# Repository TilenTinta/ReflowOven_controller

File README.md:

# Reflow Oven Controller

An open-source controller for converting a kitchen toaster oven into a reflow oven.

## Overview

This project consists of a PCB and firmware to convert a classic toaster oven into a temperature-controlled oven for PCB reflow.

### Oven Modes
- **Reflow** - Follows a predefined temperature curve for optimal PCB reflow.
- **Dry** - Maintains a defined temperature for a set duration (useful for drying components, filaments, etc.).

The oven used in this build is a budget-friendly (**40€**) **9L toaster oven** with two quartz heating elements (**BROCK TO9001B**). Despite initial concerns about heating speed, the small chamber allows it to reach the required temperatures quickly. The oven has been additionally insulated for improved performance.

A **solid-state relay (SSR)** is used for controlling the heating elements, and a **12V 5A power supply** powers the entire electronics system.

---

## PCB

The PCB is a **two-layer board** with components on only one side (**except for the LCD connector, which is on the opposite side**). The board has the **same dimensions and mounting hole positions as the LCD**, allowing them to be stacked using a **3D-printed spacer**.

The LCD used in this build is a **3.5-inch TFT LCD Display Module (320x480) with SPI Interface and Touch Screen (ILI9488 v2).**

### PCB Features
- **Safety switch** for 12V
- **Voltage measurement** (input and buck output)
- **Overtemperature protection** via NTC sensor
- **Input protection** (fuse and reverse polarity protection)
- **Max input voltage: 23V**
- **AUX1 and AUX2** (can handle up to 45V and 500mA, but limited by PCB input voltage)
- **Supports up to two solid-state relays (SSRs)** (PWM amplitude matches input voltage)
- **Supports up to two K-type thermocouples (MAX31855)**
- **Raw USART output & USB output (CH340G)** for monitoring and calibration
- **USB OTG support** (requires core clock adjustment, affecting timer parameters)
- **External 2MB flash (W25Q16JVSNIQ)** for GUI and fonts
- **SWD port** for programming
- **Buzzer**
- **MCU: STM32F411CEU6**

---

## 3D Models

All parts are printed from **PC plastic** using an **FDM 3D printer**. Alternative plastics can be used, but they must withstand high temperatures. There are two different options for electronics assembly mounting:
- Inside the oven as is in my case. For that you only need to print **Front_frame**

- On the side of the oven. For that you need to print three parts with **external** at the end of model names. Base that screws to the frame has teeth that allows preset angles. For rigit mount use only screw and nut, but you can add a spring under screw head. That will allow setting the angle later.

---

## External Loader

The **External Loader** is a necessary part of the program. It allows **CubeIDE** to upload data (GUI and fonts) to the external flash chip. If you use a different flash chip, modifications are required to meet the new chip's recommendations. The loader program must be included in the main firmware/IDE.

---

## Firmware

The firmware is not fully compatible with the latest version of the PCB. This update addresses mistakes found in the initial version of the board.

### Missing Features
- **Read input voltage**
- **Read buck voltage**
- **Read NTC sensor**
- **Safety switch** (implemented in code but not tested)

For the GUI, **TouchGFX** with standard elements is used. The only custom file is the **background**.

### External Libraries Used
The libraries for **LCD (with touch)** and **external flash (External Loader)** are not originally written by me but include minor modifications to fit this build. The original work was done by **maudeve-it**:

#### LCD Library:
- [YouTube Video](https://www.youtube.com/watch?v=g1siKaPox88)
- [GitHub Repository](https://github.com/maudeve-it/ILI9XXX-XPT2046-STM32)

#### Flash Library:
- [YouTube Video 1](https://www.youtube.com/watch?v=PO_2ZE1NQF0&list=PL6Fwy7aR3zSlZO3OBppHSzDacE4CGgRqO&index=6)
- [YouTube Video 2](https://www.youtube.com/watch?v=KlG2doCkREM)
- [GitHub Repository](https://github.com/maudeve-it/W25Qxxx_SPI_FLASH_STM32)

---

## License
This project is open-source and available under the **MIT License**.

---

## Contributing
Contributions are welcome! Feel free to submit issues or pull requests to improve the project.

---

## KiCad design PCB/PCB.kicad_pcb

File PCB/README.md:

# PCB
PCB is two layer board with components on only one side (connector for the LCD is the only part on other side). 
It is the same size and the holes are in the same position as LCD. With 3D printed spacer can be connected together.
LCD used in these build is 3.5 inch TFT LCD Display Module (320x480) with SPI Interface and Touch Screen - ILI9488 v2<br />
PCB features are:<br />
- Safety switch for 12V
- Voltage measuring: input and buck output
- PCB temperature: NTC for overtemperature protection
- input protection: fuse and reverse polarity protected
- max. input voltage: 23V
- AUX1 and AUX2 can handle up to 45V (can't be achived becouse of PCB input voltage limit), 500mA
- up to two solid state relays - PWM amplitude is the same as input voltage
- up to two K-type thermocouple (MAX31855)
- for calibration and monitoring is available raw USART output and USB output (CH340G)
- supports USB OTG - in case of enabling that function the core clock must be changed and with that all timers parameters
- external 2MB flash (W25Q16JVSNIQ) for all GUI and fonts
- SWD for programming 
- Buzzer
- MCU: STM32F411CEU6

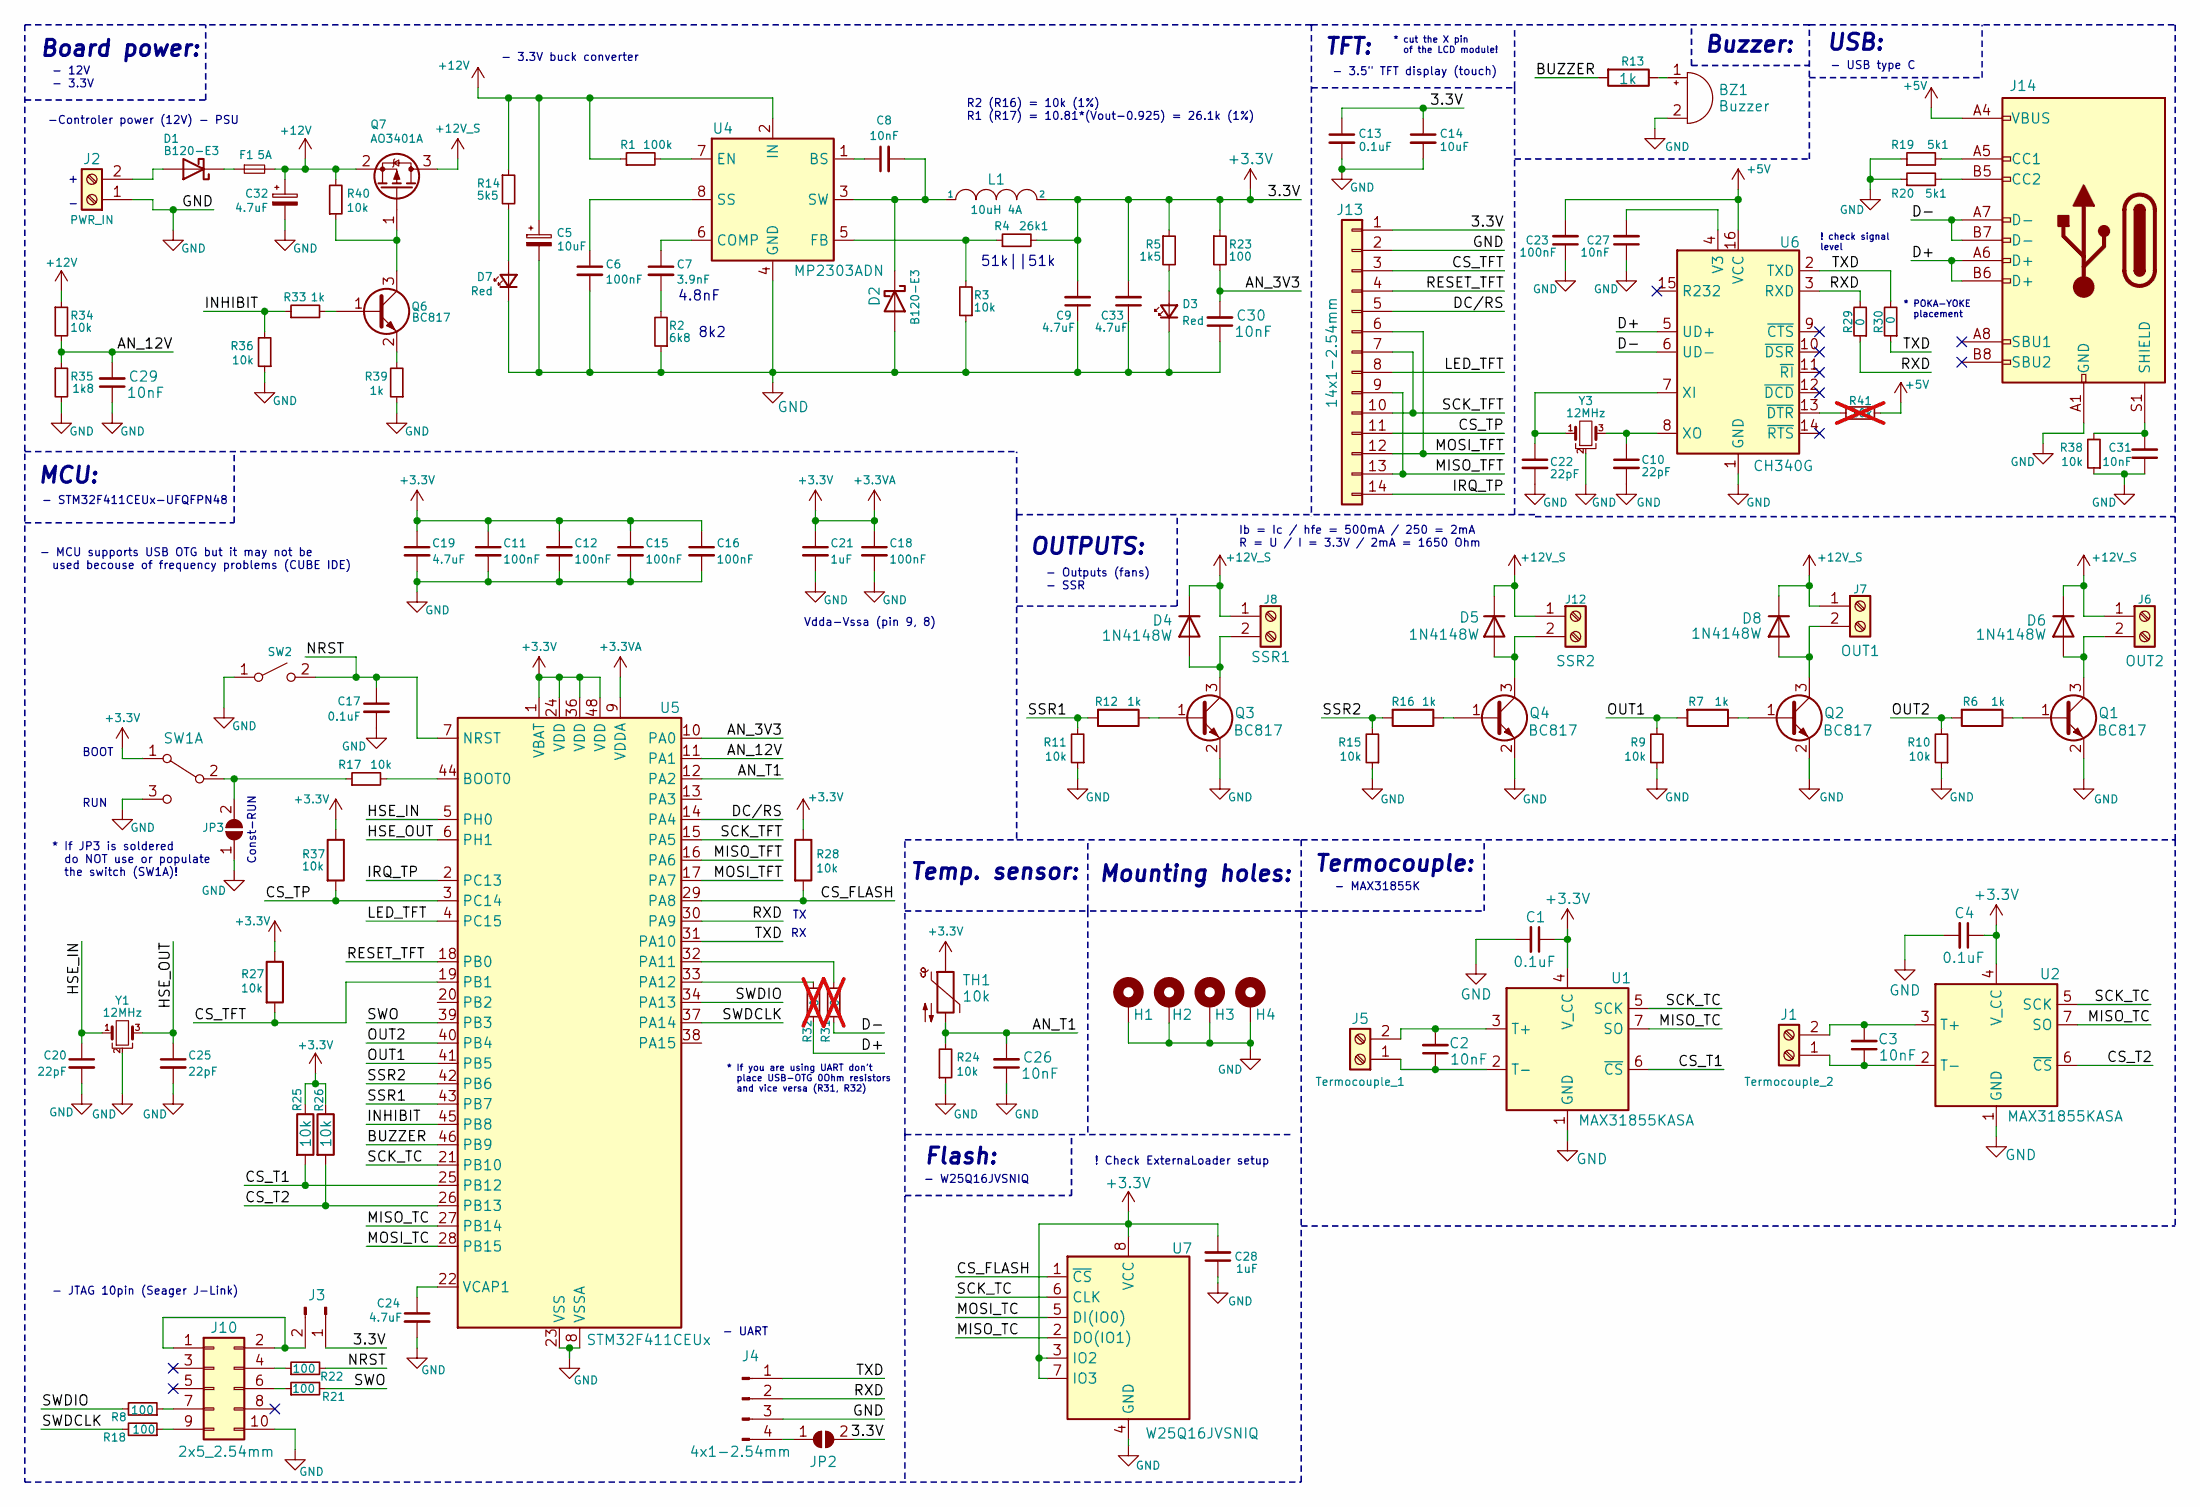
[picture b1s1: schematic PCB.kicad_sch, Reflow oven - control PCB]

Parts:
BZ1: Buzzer; Buzzer_12x9.5RM7.6
C1, C4, C13, C17: 0.1uF; C_0603_1608Metric
C2, C3, C8, C27, C31: 10nF; C_0603_1608Metric
C5: 10uF; CP_EIA-3216-10_Kemet-I
C6, C23: 100nF; C_0603_1608Metric
C7: 3.9nF; C_0603_1608Metric
C9, C33: 4.7uF; C_1206_3216Metric
C10, C20, C22, C25: 22pF; C_0402_1005Metric
C11, C12, C15, C16, C18: 100nF; C_0402_1005Metric
C14: 10uF; C_0603_1608Metric
C19, C24: 4.7uF; C_0402_1005Metric
C21: 1uF; C_0402_1005Metric
C26, C29, C30: 10nF; C_0402_1005Metric
C28: 1uF; C_0603_1608Metric
C32: 4.7uF; CP_Elec_4x5.4
D1, D2: B120-E3; D_SMA
D3, D7: Red; LED_0603_1608Metric
D4, D5, D6, D8: 1N4148W; D_SOD-123
F1: 5A; Fuse_2010_5025Metric_Pad1.52x2.65mm_HandSolder
H1, H2, H3, H4: MountingHole_Pad; MountingHole_3.2mm_M3_DIN965_Pad
J1: Termocouple_2; TerminalBlock_MetzConnect_Type055_RT01502HDWU_1x02_P5.00mm_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
J2: PWR_IN; TerminalBlock_MetzConnect_Type055_RT01502HDWU_1x02_P5.00mm_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
J3: Conn_01x02_Pin; PinHeader_1x02_P2.54mm_Vertical
J4: 4x1-2.54mm; PinHeader_1x04_P2.54mm_Vertical
J5: Termocouple_1; TerminalBlock_MetzConnect_Type055_RT01502HDWU_1x02_P5.00mm_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
J6: OUT2; TerminalBlock_MetzConnect_Type055_RT01502HDWU_1x02_P5.00mm_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
J7: OUT1; TerminalBlock_MetzConnect_Type055_RT01502HDWU_1x02_P5.00mm_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
J8: SSR1; TerminalBlock_MetzConnect_Type055_RT01502HDWU_1x02_P5.00mm_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
J10: 2x5_2.54mm; IDC-Header_2x05_P2.54mm_Vertical
J12: SSR2; TerminalBlock_MetzConnect_Type055_RT01502HDWU_1x02_P5.00mm_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
J13: 14x1-2.54mm; PinSocket_1x14_P2.54mm_Vertical
J14: USB_C_Receptacle_USB2.0; USB_C_Receptacle_XKB_U262-16XN-4BVC11
JP2, JP3: SolderJumper_2_Open; SolderJumper-2_P1.3mm_Open_TrianglePad1.0x1.5mm
L1: 10uH 4A; L_10.4x10.4_H4.8
Q1, Q2, Q3, Q4, Q6: BC817; SOT-23
Q7: AO3401A; SOT-23
R1: 100k; R_0603_1608Metric
R2: 6k8; R_0603_1608Metric
R3, R9, R10, R11, R15, R17, R24, R25, R26, R27, R28, R34, R36, R37, R38, R40: 10k; R_0603_1608Metric
R4: 26k1; R_0603_1608Metric
R5: 1k5; R_0603_1608Metric
R6, R7, R12, R13, R16, R33, R39: 1k; R_0603_1608Metric
R8, R18, R21, R22, R23: 100; R_0603_1608Metric
R14: 5k5; R_0603_1608Metric
R19, R20: 5k1; R_0603_1608Metric
R29, R30: 0; R_0603_1608Metric
R31, R32: 0; R_0603_1608Metric; not fitted
R35: 1k8; R_0603_1608Metric
R41: 10k; R_0603_1608Metric; not fitted
SW1: SW_DPDT; SW_SPDT_PCM12
SW2: SW_SPST; SW_Push_1P1T_NO_CK_KMR2
TH1: 10k; R_0603_1608Metric
U1, U2: MAX31855KASA; SOIC-8_3.9x4.9mm_P1.27mm
U4: MP2303ADN; SOIC-8-1EP_3.9x4.9mm_P1.27mm_EP2.62x3.51mm
U5: STM32F411CEUx; QFN-48-1EP_7x7mm_P0.5mm_EP5.6x5.6mm
U6: CH340G; SOIC-16_3.9x9.9mm_P1.27mm
U7: W25Q16JVSNIQ; SOIC-8_5.23x5.23mm_P1.27mm
Y1, Y3: 12MHz; Resonator_SMD_Murata_CSTxExxV-3Pin_3.0x1.1mm

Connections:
+3.3V: C1.1, C4.1, C9.2, C11.1, C12.1, C13.1, C14.1, C15.1, C16.1, C18.1, C19.1, C21.1, C28.2, C33.2, J3.1, J13.1, JP2.2 (B), L1.2, R4.2, R5.1, R23.1, R25.1, R26.1, R27.1, R28.1, R37.1, SW1.1 (A), TH1.1, U1.4 (V_CC), U2.4 (V_CC), U5.1 (VBAT), U5.9 (VDDA), U5.24 (VDD), U5.36 (VDD), U5.48 (VDD), U7.3 (IO2), U7.7 (IO3), U7.8 (VCC)
+5V: C23.2, J14.A4 (VBUS), J14.A9 (VBUS), J14.B4 (VBUS), J14.B9 (VBUS), R41.1, U6.16 (VCC)
+12V: C5.1, C32.1, F1.2, Q7.2 (S), R1.1, R14.1, R34.1, R40.2, U4.2 (IN)
+12V_S: D4.1 (K), D5.1 (K), D6.1 (K), D8.1 (K), J6.1, J7.1, J8.1, J12.1, Q7.3 (D)
/AN_3V3: C30.2, R23.2, U5.10 (PA0)
/AN_12V: C29.2, R34.2, R35.1, U5.11 (PA1)
/AN_T1: C26.2, R24.2, TH1.2, U5.12 (PA2)
/BUZZER: R13.2, U5.46 (PB9)
/CS_FLASH: R28.2, U5.29 (PA8), U7.1 (~CS)
/CS_T1: R25.2, U1.6 (~CS), U5.25 (PB12)
/CS_T2: R26.2, U2.6 (~CS), U5.26 (PB13)
/CS_TFT: J13.3, R27.2, U5.19 (PB1)
/CS_TP: J13.11, R37.2, U5.3 (PC14)
/D+: J14.A6 (D+), J14.B6 (D+), R32.1, U6.5 (UD+)
/D-: J14.A7 (D-), J14.B7 (D-), R31.1, U6.6 (UD-)
/DC/RS: J13.5, U5.14 (PA4)
/HSE_IN: C20.1, U5.5 (PH0), Y1.1
/HSE_OUT: C25.1, U5.6 (PH1), Y1.3
/INHIBIT: R33.1, R36.2, U5.45 (PB8)
/IRQ_TP: J13.14, U5.2 (PC13)
/LED_TFT: J13.8, U5.4 (PC15)
/MISO_TC: U1.7 (SO), U2.7 (SO), U5.27 (PB14), U7.2 (DO(IO1))
/MISO_TFT: J13.9, J13.13, U5.16 (PA6)
/MOSI_TC: U5.28 (PB15), U7.5 (DI(IO0))
/MOSI_TFT: J13.6, J13.12, U5.17 (PA7)
/NRST: C17.1, R22.2, SW2.2 (B), U5.7 (NRST)
/OUT1: R7.2, R9.2, U5.41 (PB5)
/OUT2: R6.2, R10.2, U5.40 (PB4)
/RESET_TFT: J13.4, U5.18 (PB0)
/RXD: J4.2, R29.1, R29.2, U5.30 (PA9), U6.3 (RXD)
/SCK_TC: U1.5 (SCK), U2.5 (SCK), U5.21 (PB10), U7.6 (CLK)
/SCK_TFT: J13.7, J13.10, U5.15 (PA5)
/SSR1: R11.2, R12.2, U5.43 (PB7)
/SSR2: R15.2, R16.2, U5.42 (PB6)
/SWDCLK: R18.2, U5.37 (PA14)
/SWDIO: R8.2, U5.34 (PA13)
/SWO: R21.2, U5.39 (PB3)
/TXD: J4.1, R30.1, R30.2, U5.31 (PA10), U6.2 (TXD)
GND: BZ1.2 (+), C1.2, C4.2, C5.2, C6.2, C9.1, C10.2, C11.2, C12.2, C13.2, C14.2, C15.2, C16.2, C17.2, C18.2, C19.2, C20.2, C21.2, C22.2, C23.1, C24.2, C25.2, C26.1, C27.1, C28.1, C29.1, C30.1, C31.1, C32.2, C33.1, D2.2 (A), D3.1 (K), D7.1 (K), H1.1, H2.1, H3.1, H4.1, J2.1, J4.3, J10.10, J13.2, J14.A1 (GND), J14.A12 (GND), J14.B1 (GND), J14.B12 (GND), JP3.1 (A), Q1.2 (E), Q2.2 (E), Q3.2 (E), Q4.2 (E), R2.1, R3.1, R9.1, R10.1, R11.1, R15.1, R19.1, R20.1, R24.1, R35.2, R36.1, R38.1, R39.1, SW1.3 (C), SW2.1 (A), U1.1 (GND), U2.1 (GND), U4.4 (GND), U5.8 (VSSA), U5.23 (VSS), U5.35 (VSS), U5.47 (VSS), U5.49 (VSS), U6.1 (GND), U7.4 (GND), Y1.2, Y3.2
unnamed: BZ1.1 (-), R13.1
unnamed: C7.2, R2.2
unnamed: D1.2 (A), J2.2
unnamed: D1.1 (K), F1.1
unnamed: C8.2, D2.1 (K), L1.1, U4.3 (SW)
unnamed: D3.2 (A), R5.2
unnamed: D4.2 (A), J8.2, Q3.3 (C)
unnamed: D5.2 (A), J12.2, Q4.3 (C)
unnamed: D6.2 (A), J6.2, Q1.3 (C)
unnamed: D7.2 (A), R14.2
unnamed: D8.2 (A), J7.2, Q2.3 (C)
unnamed: C3.1, J1.1, U2.2 (T-)
unnamed: C3.2, J1.2, U2.3 (T+)
unnamed: J4.4, JP2.1 (A)
unnamed: C2.1, J5.1, U1.2 (T-)
unnamed: C2.2, J5.2, U1.3 (T+)
unnamed: J3.2, J10.1, J10.2
unnamed: J10.4, R22.1
unnamed: J10.6, R21.1
unnamed: J10.7, R8.1
unnamed: J10.9, R18.1
unnamed: J14.A5 (CC1), R19.2
unnamed: J14.B5 (CC2), R20.2
unnamed: C31.2, J14.S1 (SHIELD), R38.2
unnamed: JP3.2 (B), R17.1, SW1.2 (B)
unnamed: Q1.1 (B), R6.1
unnamed: Q2.1 (B), R7.1
unnamed: Q3.1 (B), R12.1
unnamed: Q4.1 (B), R16.1
unnamed: Q6.1 (B), R33.2
unnamed: Q6.3 (C), Q7.1 (G), R40.1
unnamed: Q6.2 (E), R39.2
unnamed: C8.1, U4.1 (BS)
unnamed: C7.1, U4.6 (COMP)
unnamed: R1.2, U4.7 (EN)
unnamed: R3.2, R4.1, U4.5 (FB)
unnamed: C6.1, U4.8 (SS)
unnamed: R17.2, U5.44 (BOOT0)
unnamed: R31.2, U5.32 (PA11)
unnamed: R32.2, U5.33 (PA12)
unnamed: C24.1, U5.22 (VCAP1)
unnamed: C27.2, U6.4 (V3)
unnamed: C22.1, U6.7 (XI), Y3.1
unnamed: C10.1, U6.8 (XO), Y3.3
unnamed: R41.2, U6.13 (~DTR)

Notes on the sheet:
Ib = Ic / hfe = 500mA / 250 = 2mA R = U / I = 3.3V / 2mA = 1650 Ohm
R2 (R16) = 10k (1%) R1 (R17) = 10.81*(Vout-0.925) = 26.1k (1%)
8k2
BOOT
Temp. sensor:
* POKA-YOKE placement
! check signal level
MCU:
Vdda-Vssa (pin 9, 8)
Buzzer:
* cut the X pin of the LCD module!
* If JP3 is soldered do NOT use or populate the switch (SW1A)!
4.8nF
- MAX31855K
Termocouple:
- UART
OUTPUTS:
Board power:
- JTAG 10pin (Seager J-Link)
- MCU supports USB OTG but it may not be used becouse of frequency problems (CUBE IDE)
TFT:
- Outputs (fans) - SSR
! Check ExternaLoader setup
- 12V - 3.3V
- 3.3V buck converter
- 3.5" TFT display (touch)
USB:
Mounting holes:
- USB type C
Flash:
-Controler power (12V) - PSU
Const-RUN
51k||51k
* If you are using UART don't place USB-OTG 0Ohm resistors and vice versa (R31, R32)
- W25Q16JVSNIQ
RUN
- STM32F411CEUx-UFQFPN48

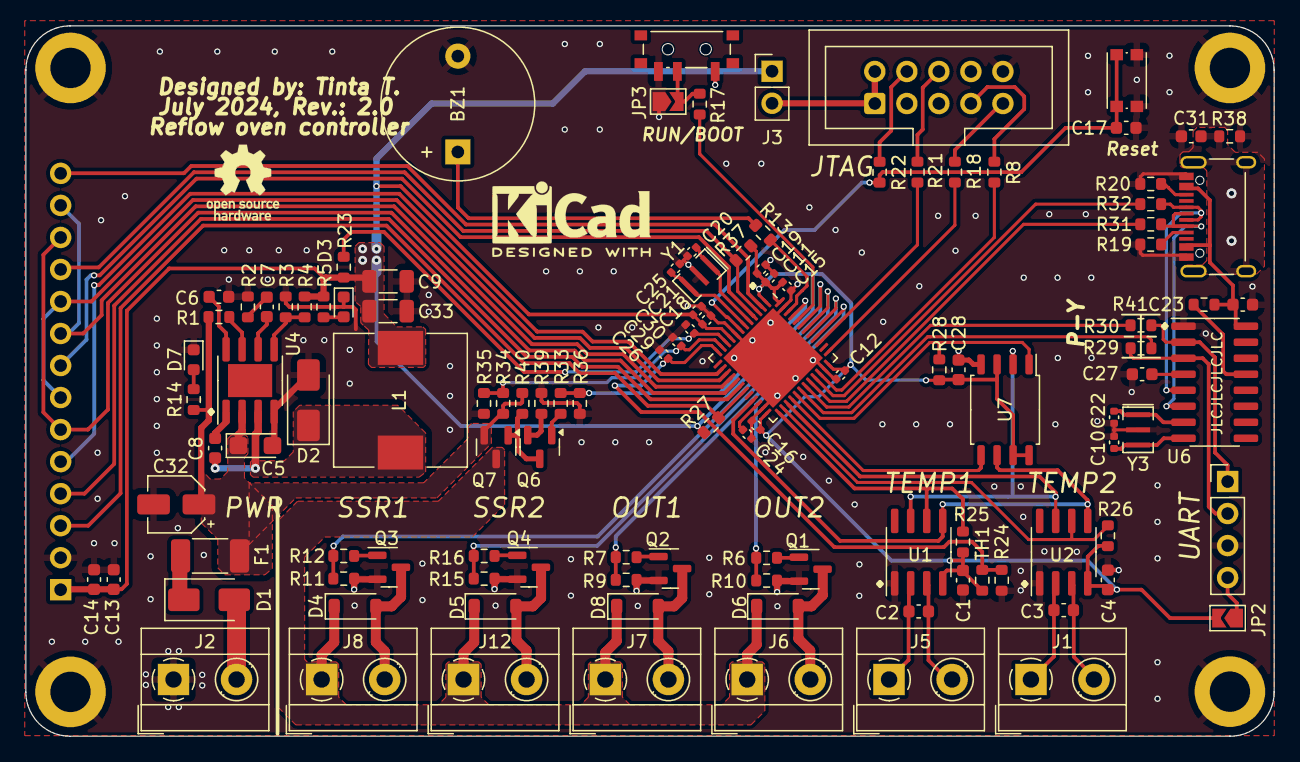
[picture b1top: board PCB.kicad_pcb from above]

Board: 2 copper layers, 99.0 x 56.3 mm, 120 parts (1 on the bottom side), 84 nets.

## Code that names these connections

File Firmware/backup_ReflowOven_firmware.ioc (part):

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Mcu.Name=STM32F411C(C-E)Ux
Mcu.Package=UFQFPN48
Mcu.UserName=STM32F411CEUx
PA0-WKUP.GPIOParameters=GPIO_PuPd,GPIO_Label
PA0-WKUP.GPIO_Label=TOUCH_INT
PA0-WKUP.GPIO_PuPd=GPIO_PULLUP
PA0-WKUP.Signal=GPXTI0
PA1.GPIOParameters=GPIO_Speed,PinState,GPIO_PuPd,GPIO_Label
PA1.GPIO_Label=TOUCH_CS
PA1.GPIO_PuPd=GPIO_NOPULL
PA1.GPIO_Speed=GPIO_SPEED_FREQ_HIGH
PA1.PinState=GPIO_PIN_SET
PA1.Signal=GPIO_Output
PA10.Mode=Asynchronous
PA10.Signal=USART1_RX
PA13.Mode=Serial_Wire
PA13.Signal=SYS_JTMS-SWDIO
PA14.Mode=Serial_Wire
PA14.Signal=SYS_JTCK-SWCLK
PA15.GPIOParameters=GPIO_Speed,PinState,GPIO_Label
PA15.GPIO_Label=FLASH_CS
PA15.GPIO_Speed=GPIO_SPEED_FREQ_LOW
PA15.PinState=GPIO_PIN_SET
PA15.Signal=GPIO_Output
PA2.GPIOParameters=GPIO_Label
PA2.GPIO_Label=DISPL_LED
PA2.Signal=GPIO_Output
PA4.GPIOParameters=GPIO_Speed,GPIO_Label
PA4.GPIO_Label=DISPL_DC
PA4.GPIO_Speed=GPIO_SPEED_FREQ_LOW
PA4.Signal=GPIO_Output
PA5.GPIOParameters=GPIO_Label
PA5.GPIO_Label=DISPL_SCK
PA5.Mode=Full_Duplex_Master
PA5.Signal=SPI1_SCK
PA6.GPIOParameters=GPIO_Label
PA6.GPIO_Label=TOUCH_MISO
PA6.Mode=Full_Duplex_Master
PA6.Signal=SPI1_MISO
PA7.GPIOParameters=GPIO_Label
PA7.GPIO_Label=DISPL_MOSI
PA7.Mode=Full_Duplex_Master
PA7.Signal=SPI1_MOSI
PA8.GPIOParameters=GPIO_Label
PA8.GPIO_Label=AN_T1
PA8.Signal=GPIO_Analog
PA9.Mode=Asynchronous
PA9.Signal=USART1_TX
PB0.GPIOParameters=GPIO_Speed,GPIO_Label
PB0.GPIO_Label=DISPL_RST
PB0.GPIO_Speed=GPIO_SPEED_FREQ_VERY_HIGH
PB0.Signal=GPIO_Output
PB1.GPIOParameters=GPIO_Speed,PinState,GPIO_PuPd,GPIO_Label
PB1.GPIO_Label=DISPL_CS
PB1.GPIO_PuPd=GPIO_NOPULL
PB1.GPIO_Speed=GPIO_SPEED_FREQ_HIGH
PB1.PinState=GPIO_PIN_SET
PB1.Signal=GPIO_Output
PB10.GPIOParameters=GPIO_Label
PB10.GPIO_Label=FLASH_SCK
PB10.Mode=Full_Duplex_Master
PB10.Signal=SPI2_SCK
PB12.GPIOParameters=PinState,GPIO_Label
PB12.GPIO_Label=TERMO1_CS
PB12.PinState=GPIO_PIN_SET
PB12.Signal=GPIO_Output
PB13.GPIOParameters=PinState,GPIO_Label
PB13.GPIO_Label=TERMO2_CS
PB13.PinState=GPIO_PIN_SET
PB13.Signal=GPIO_Output
PB14.GPIOParameters=GPIO_Label
PB14.GPIO_Label=FLASH_MISO
PB14.Mode=Full_Duplex_Master
PB14.Signal=SPI2_MISO
PB15.GPIOParameters=GPIO_Label
PB15.GPIO_Label=FLASH_MOSI
PB15.Mode=Full_Duplex_Master
PB15.Signal=SPI2_MOSI
PB2.GPIOParameters=GPIO_Label
PB2.GPIO_Label=AN_3V3
PB2.Signal=GPIO_Analog
PB4.GPIOParameters=GPIO_Label
PB4.GPIO_Label=AUX_OUT2
PB4.Signal=GPIO_Output
PB5.GPIOParameters=GPIO_Label
PB5.GPIO_Label=AUX_OUT1
PB5.Signal=GPIO_Output
PB6.GPIOParameters=GPIO_Speed,GPIO_Label
PB6.GPIO_Label=SSR2
PB6.GPIO_Speed=GPIO_SPEED_FREQ_MEDIUM
PB6.Signal=S_TIM4_CH1
PB7.GPIOParameters=GPIO_Speed,GPIO_Label
PB7.GPIO_Label=SSR1
PB7.GPIO_Speed=GPIO_SPEED_FREQ_MEDIUM
PB7.Signal=S_TIM4_CH2
PC13-ANTI_TAMP.GPIOParameters=GPIO_Label
PC13-ANTI_TAMP.GPIO_Label=AN_12V
PC13-ANTI_TAMP.Signal=GPIO_Analog
PC14-OSC32_IN.GPIOParameters=GPIO_Label
PC14-OSC32_IN.GPIO_Label=INHIBIT
PC14-OSC32_IN.Signal=GPIO_Output
PC15-OSC32_OUT.GPIOParameters=GPIO_Label
PC15-OSC32_OUT.GPIO_Label=BUZZER
PC15-OSC32_OUT.Signal=GPIO_Output
PH0\ -\ OSC_IN.Mode=HSE-External-Oscillator
PH0\ -\ OSC_IN.Signal=RCC_OSC_IN
PH1\ -\ OSC_OUT.Mode=HSE-External-Oscillator
PH1\ -\ OSC_OUT.Signal=RCC_OSC_OUT
RCC.HSE_VALUE=12000000
RCC.SYSCLKFreq_VALUE=100000000
RCC.SYSCLKSource=RCC_SYSCLKSOURCE_PLLCLK
board=custom

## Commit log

2024-05-21 first commit, PCB done(not tested yet), firmware started(LCD works, touch screen works)
2024-06-22 PCB done and ordered, touch screen and TFT works, flash works, EdternalLoader, GUI partialy done
2024-06-22 gitignore
2024-07-27 PCB works (Problems: safety switch, analog inputs mistake), ExternalLoader works, gui in progress
2024-07-27 SW: 5Hz reading loop, averaging temperature, gui live temperature, time counter
2024-07-30 timer corrected, PID base
2024-08-05 PCB update, firmaware
    usb problem -> repaired
    firmware update: pid, PWM, gui
2024-08-05 Firmware update
    simplified PID, PID tuned, gui rapair and added features
2024-08-06 SW update
    flash save variables (not finished)
    reflow profile values calculation
2024-08-07 SW Update
    working reflow, following the temperature profile, changed and added features to plots, active reflow stage indicator
2024-08-07 SW Update
    Over temperature protection
2024-08-11 SW update
    thermal runaway, better reflow reference following, detect first boot and init presset values
2024-08-11 SW update
    saving variables to flash and allowing user to reset them from program when uploading, repaired bugs in reflow profile settings
2024-08-11 Create LICENSE
2024-08-11 documentation
2024-08-12 Documentation update
2024-08-12 documentation update...
2024-09-14 bugfix
    Reflow profile - temperature can now be set to 0, time of cooling is not limited to 300
2024-09-14 bugfix, updates
    bugfix: reflow timing, plot generating
    updates: start/stop buttons are now one button
2024-09-14 Update
    allow menu usage between oven use
2024-09-14 bugfix
    keep start/stop button state when returning to main screen
2024-09-15 Bugfix
    plot repair and variable init after finished reflow
2025-02-15 Readme update
2025-07-20 Bugfix
    changed reset values of plot x-axis numbers
2025-07-25 update
    added STEP files and external electronics case
2025-07-25 update
    readme
